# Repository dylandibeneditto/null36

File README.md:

<picture align="center">
    
</picture>

<h1 align="center">null36</h1>

36-Key wireless split ortho column-staggered MX keyboard. Controlled by any Nice!Nano V2 compatible MCU, and support for SSD1306 OLED displays.

# Layout and Keymap

# PCB

[/pcbs](./pcbs)
> This PCB is reversible. When assembling, solder together the pads above the OLED display header, the pads next to the battery jack (the jack goes on the underside of the pcb), and diodes can go on either the front or back, as long as they follow the direction of the silkscreen

# Case

[/cases](./cases)

# Photos

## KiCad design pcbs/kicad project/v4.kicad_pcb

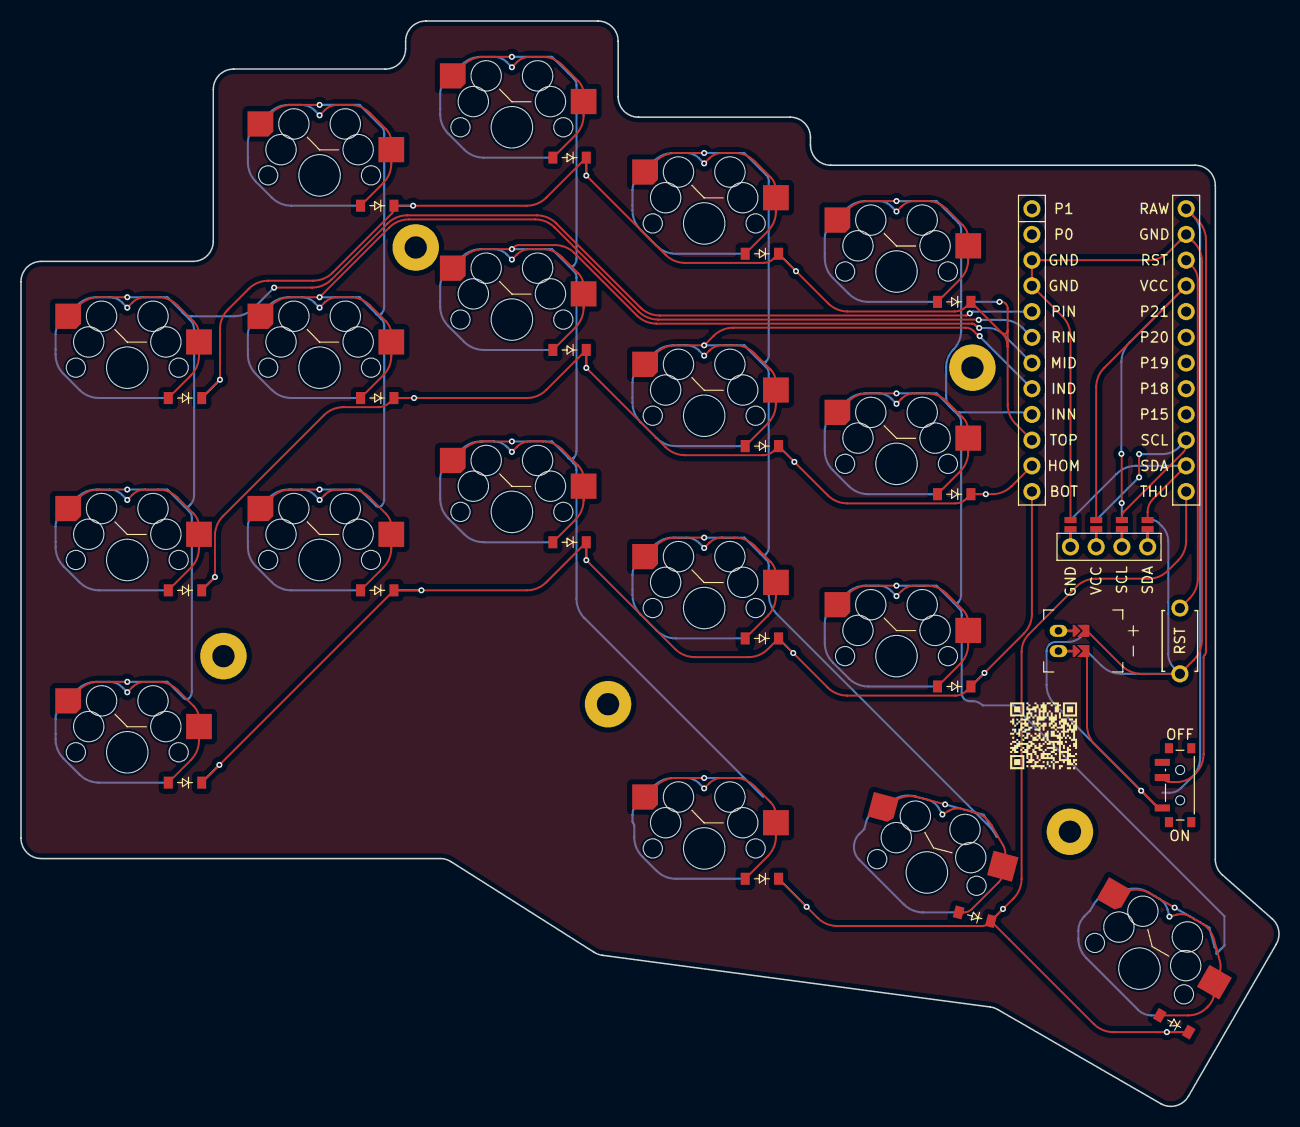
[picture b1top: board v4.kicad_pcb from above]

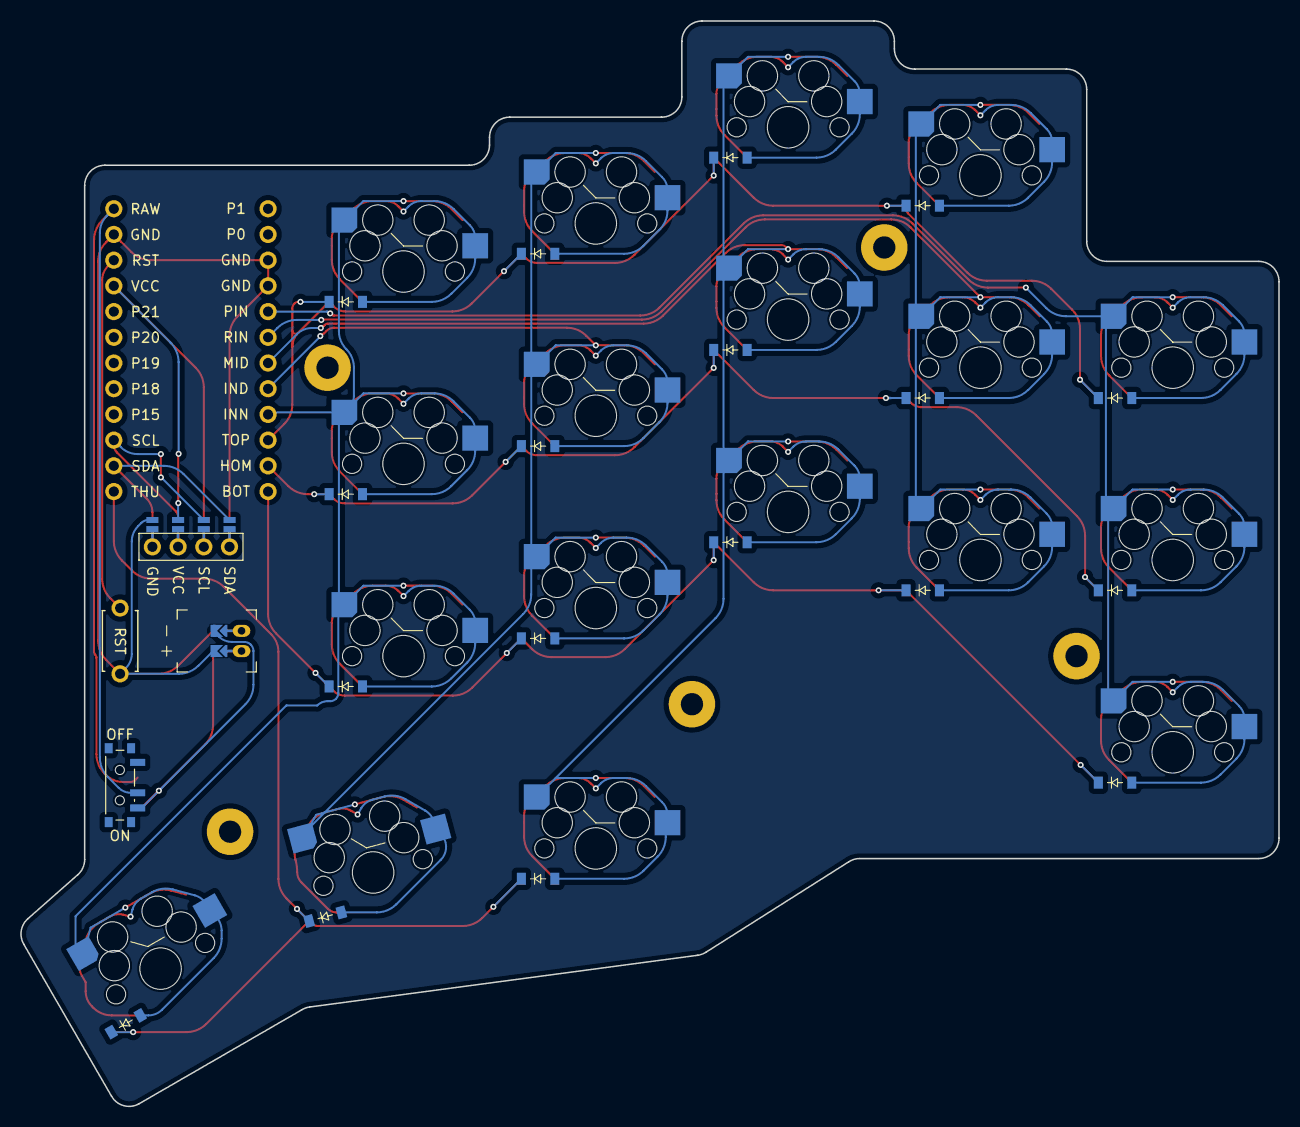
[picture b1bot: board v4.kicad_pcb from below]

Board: 2 copper layers, 124.3 x 107.2 mm, 46 parts (18 on the bottom side), 40 nets.

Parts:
D1, D2, D3, D4, D5, D6, D7, D8, D9, D10, D11, D12, D13, D14, D15, D16, D17, D18: diode_tht_sod123
DISP1: display_ssd1306
JST1: battery_connector_jst_ph_2
MCU1: mcu_supermini_nrf52840
MH1, MH2, MH3, MH4, MH5: mounting_hole_npth
PWR1: power_switch_smd_side
RST1: reset_switch_tht_top
S1, S2, S3, S4, S5, S6, S7, S8, S9, S10, S11, S12, S13, S14, S15, S16, S17, S18: switch_mx

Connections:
BAT_P: JST1.1, PWR1.1, PWR1.3
BOT: D1.1, D4.1, D7.1, D10.1, D13.1, MCU1.13
DISP1_1: DISP1.1, DISP1.10, DISP1.23
DISP1_2: DISP1.2, DISP1.11, DISP1.22
DISP1_3: DISP1.3, DISP1.12, DISP1.21
DISP1_4: DISP1.4, DISP1.13, DISP1.20
GND: DISP1.14, DISP1.24, JST1.2, MCU1.2, MCU1.21, MCU1.22, RST1.2
HOM: D2.1, D5.1, D8.1, D11.1, D14.1, MCU1.14
IND: MCU1.17, S10.2, S11.2, S12.2, S17.2
IND_BOT: D10.2, S10.1
IND_HOM: D11.2, S11.1
IND_THU: D17.2, S17.1
IND_TOP: D12.2, S12.1
INN: MCU1.16, S13.2, S14.2, S15.2, S18.2
INN_BOT: D13.2, S13.1
INN_HOM: D14.2, S14.1
INN_THU: D18.2, S18.1
INN_TOP: D15.2, S15.1
JST1_1: JST1.11, JST1.21, JST1.31
JST1_2: JST1.12, JST1.22, JST1.32
MID: MCU1.18, S7.2, S8.2, S9.2, S16.2
MID_BOT: D7.2, S7.1
MID_HOM: D8.2, S8.1
MID_THU: D16.2, S16.1
MID_TOP: D9.2, S9.1
PIN: MCU1.20, S1.2, S2.2, S3.2
PIN_BOT: D1.2, S1.1
PIN_HOM: D2.2, S2.1
PIN_TOP: D3.2, S3.1
RAW: MCU1.1, PWR1.2
RIN: MCU1.19, S4.2, S5.2, S6.2
RIN_BOT: D4.2, S4.1
RIN_HOM: D5.2, S5.1
RIN_TOP: D6.2, S6.1
RST: MCU1.3, RST1.1
SCL: DISP1.16, DISP1.26, MCU1.10
SDA: DISP1.17, DISP1.27, MCU1.11
THU: D16.1, D17.1, D18.1, MCU1.12
TOP: D3.1, D6.1, D9.1, D12.1, D15.1, MCU1.15
VCC: DISP1.15, DISP1.25, MCU1.4

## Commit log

2026-01-26 initial pcb design
2026-01-26 v2 of pcb
2026-01-26 v3 of pcb
2026-01-26 rearrange directory
2026-01-26 v3 pcb design
2026-01-29 v4 pcb design
2026-01-30 exporting and start of case
2026-01-30 added README
2026-01-30 add layout
2026-01-30 pcb pictures added
2026-01-30 case images
2026-01-30 cleanup repo formatting
2026-01-30 add gitignore
2026-01-30 remove ds_store
2026-03-01 assembly and keymap
2026-03-01 fix image reference
